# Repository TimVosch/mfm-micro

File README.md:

# Multiflexmeter Micro

A small, long lasting measurement device with hotswappable zero-configuration peripherals.

## Hardware development

Developed using KiCAD. Files are in the `hardware` folder.

## Firmware development

Developed using PlatformIO and the STM32CubeL0 library with CMSIS.

```
git clone https://github.com/TimVosch/mfm-micro.git
cd mfm-micro
git submodule update --init
```

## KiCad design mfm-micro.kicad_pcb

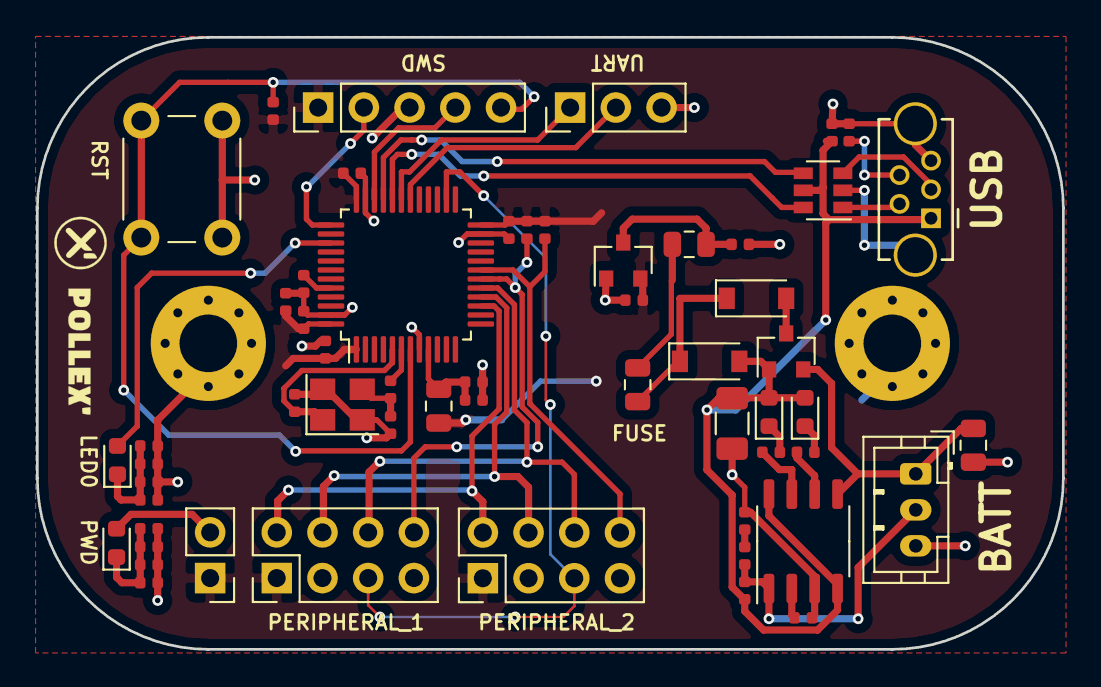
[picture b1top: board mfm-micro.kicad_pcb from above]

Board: 4 copper layers, 57.0 x 34.0 mm, 59 parts (0 on the bottom side), 40 nets.

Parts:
C1: 4.7u; C_0402_1005Metric
C2, C3, C11: 1u; C_0402_1005Metric
C4: 10u; C_0805_2012Metric
C5: 10u; C_0402_1005Metric
C6, C7, C8, C9, C10: 100n; C_0402_1005Metric
C12, C13: 12p; C_0402_1005Metric
D1, D4: B5819W; D_SOD-123
D2, D5: Green; LED_0603_1608Metric
D3, D6: Red; LED_0603_1608Metric
F1: Fuse_Small; Fuse_0805_2012Metric
FB1: 100/100MHz; L_0805_2012Metric
FB2: 100 @ 100MHz; L_0805_2012Metric
H1, H2: MountingHole_Pad; MountingHole_3.2mm_M3_Pad_Via
J1: USB_B_Mini; USB_Mini-B_Tensility_54-00023_Vertical_CircularHoles
J2: JST PH 3; JST_PH_B3B-PH-K_1x03_P2.00mm_Vertical
J3: SWD_connector; PinHeader_1x05_P2.54mm_Vertical
J4: Conn_01x03; PinHeader_1x03_P2.54mm_Vertical
P1: Peripheral1_connector; PinHeader_2x04_P2.54mm_Vertical
P2: Peripheral2_connector; PinHeader_2x04_P2.54mm_Vertical
Q1: AO3401A; SOT-23
R1: 10k; R_1206_3216Metric
R2: 5.1k; R_0402_1005Metric
R3, R5: 100; R_0402_1005Metric
R4, R9, R11, R20, R21: 10k; R_0402_1005Metric
R6: 56k; R_0402_1005Metric
R7: 22k; R_0402_1005Metric
R8: 1.5k; R_0402_1005Metric
R10: 680; R_0402_1005Metric
R12, R13, R14, R15, R16, R17, R18, R19: 130; R_0402_1005Metric
SW1: SW_RST; SW_PUSH_6mm
SW4: PWR_LED_Switch; PinHeader_1x02_P2.54mm_Vertical
U1: XC6206P332MR; SOT-23
U2: TP4056; SOP-8_3.9x4.9mm_P1.27mm
U3: USBLC6-2P6; SOT-23-6
U4: STM32L072CBTx; LQFP-48_7x7mm_P0.5mm
XOSC1: 16MHz; Crystal_SMD_3225-4Pin_3.2x2.5mm

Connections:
+3.3VA: C10.1, C11.1, FB2.2, U4.9
+3V3: C3.1, C5.1, C6.1, C7.1, C8.1, C9.1, FB2.1, J3.1, P1.1, P2.1, R9.1, R20.1, R21.1, SW4.1, U1.2, U4.1, U4.24, U4.36, U4.48
+BATT: C4.1, J2.1, Q1.2, U2.5
BATT_T: J2.2, R2.2, R6.1, U2.1
BOOT0: R11.1, U4.44
GND: C1.2, C2.2, C3.2, C4.2, C5.2, C6.2, C7.2, C8.2, C9.2, C10.2, C11.2, C12.2, C13.2, H1.1, H2.1, J1.5, J1.6, J2.3, J3.3, J4.3, P1.3, P2.3, R1.2, R4.2, R7.2, R8.1, R11.2, R12.1, R13.1, R14.1, R15.1, R16.1, R17.1, R18.1, R19.1, SW1.1, U1.1, U2.3, U3.2, U4.8, U4.23, U4.35, U4.47, XOSC1.2, XOSC1.4
LED0: D5.2, U4.39
NRST: J3.5, R9.2, SW1.2, U4.7
unnamed: C2.1, FB1.2, U1.3
unnamed: C13.1, R10.1, XOSC1.3
unnamed: D2.1, R5.1
unnamed: D3.1, R3.1
unnamed: D4.2, Q1.3
unnamed: D5.1, R12.2, R13.2, R14.2, R15.2
unnamed: D6.1, R16.2, R17.2, R18.2, R19.2
unnamed: D6.2, SW4.2
unnamed: F1.2, FB1.1
unnamed: J1.4, R4.1
unnamed: R3.2, U2.7
unnamed: R5.2, U2.6
unnamed: R6.2, R7.1
unnamed: R8.2, U2.2
P_EXTI: P1.5, P2.5, U4.26
SPI_MISO: P1.4, P2.4, U4.16
SPI_MOSI: P1.6, P2.6, U4.17
SPI_SCK: P1.2, P2.2, U4.15
SPI_SS1: P1.8, R20.2, U4.18
SPI_SS2: P2.8, R21.2, U4.19
SWCLK: J3.2, U4.37
SWDIO: J3.4, U4.34
UART1_RX: J4.1, U4.31
UART1_TX: J4.2, U4.30
USB_CONN_D+: J1.3, U3.3
USB_CONN_D-: J1.2, U3.1
USB_D+: U3.4, U4.33
USB_D-: U3.6, U4.32
VBUS: C1.1, D1.2, D2.2, D3.2, J1.1, Q1.1, R1.1, R2.1, U2.4, U2.8, U3.5
VCC: D1.1, D4.1, F1.1
XOSC_IN: C12.1, U4.5, XOSC1.1
XOSC_OUT: R10.2, U4.6

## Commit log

2020-09-14 Place components on PCB
2020-09-14 Higher quality exports
2020-09-15 Rerout and new exports
2020-09-24 Reorganize project structure
2020-09-24 Add PlatformIO + MCU startup , ld script
2020-09-24 Add main header
2020-09-28 Use stm32 generated lib
2020-09-29 Update file names
2020-09-29 Remove implicit ddeclaration
2020-09-29 SPI test
2020-10-13 feat: Implement I2C BitBang single byte write
2020-10-14 feat(I2C): Swap and implement write for byte array
    Rename function to function and implement writing a
    byte array in new func
2020-10-15 Refactor: update i2c driver
2020-10-26 refactor(i2c): rename sda/scl clear/set to low/high
2020-11-04 Update docs
2020-11-04 Update pio version
2020-11-04 Update I2C driver functions
2020-11-06 Move to drivers folder, direct IO register access
2020-11-06 Remove unused state
2020-11-06 Refactor i2c_driver.cpp to i2c.cpp
2020-11-06 Implement basic SMBus functions
2020-11-06 refactor(u2c/smbus): Move write/read bytes to i2c driver
    Moves the i2c_read_bytes and i2c_write_bytes functions from the smbus
    driver to the i2c driver as read_bytes and write_bytes respectively
2020-11-06 fix(smbus): Allow quick-command 1 or 0
    Previous implementation only allowed to send a write bit (one), however
    this bit can also be read bit (zero)
2020-11-07 feat(smbus): Implement PEC
2020-11-07 style(i2c): Comments
2020-11-07 feat(smbus): I2CDriver wrapper for SMBus
    Provides a new SMBus_I2C class which is just like the I2CDriver except
    also calculates the CRC for messages
2020-11-07 feat(smbus): SMBus_I2C hold R/W direction and pending ACK
    The SMBus_I2C wrapper now holds the current transaction direction and
    whether there is an acknowledgement pending.
    The pending ack is only applicable when reading bytes, because written
    bytes are acked in the I2CDriver
2020-11-07 feat(smbus): getters for cur_dir and pend_ack in SMBus_I2C
    Rename pend_ack and cur_dir to pending_ack and current_direction for the
    SMBus_I2C wrapper.
    Also provide getters for both variables.
2020-11-07 refactor(smbus): Use smbus_i2c to rework smubs::end function
    Rework the `end()` function for smbus transactions using the new
    features provided in the smbus_i2c wrapper.
2020-11-08 perf(i2c): Improve utility functions
    Remove '> 0' check on read_sda read_scl
    Drop us_delay if delay <= 2 us
2020-11-08 feat(i2c): Allow clock_stretch on each bit
2020-11-08 chore(main): Update demo code
2020-11-08 refactor(i2c): Rename I2CDriver to I2C_Master
2020-11-09 fix(smbus): Have all commands use 'end()'
2020-11-10 refactor: Port system_startup assembly to C
2020-11-10 docs(smbus): fix quick_command doc
2020-11-12 Feature(ops): Add github-action
